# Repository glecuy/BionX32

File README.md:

# BionX32  stm32 controller for BionX ebike motor

The BionX motor has originally a built-in controller. This project aims to replace embedde electronics by an external controller.
Regular 24V controller with square waves doesn't provide good enough results, this is a new attempt with a FOC implementation.

## Project Content

3 phases output,

3 hall sensors input,

One Shunt current measurement,

Interface for S866 Display.

PAS input,

Brake input

Core code is generated thanks to ST micro graphical tools. (X-CUBE-MCSDK)
then adapted to STM32F103C8Tx

## Hardware description

STM32 module
MOSFET module
Main pcb
S866 display

## Credits  & Resources
STM32CubeIDE

STM32 MC SDK (motor control software development kit) : Gived up (Did not work for me)

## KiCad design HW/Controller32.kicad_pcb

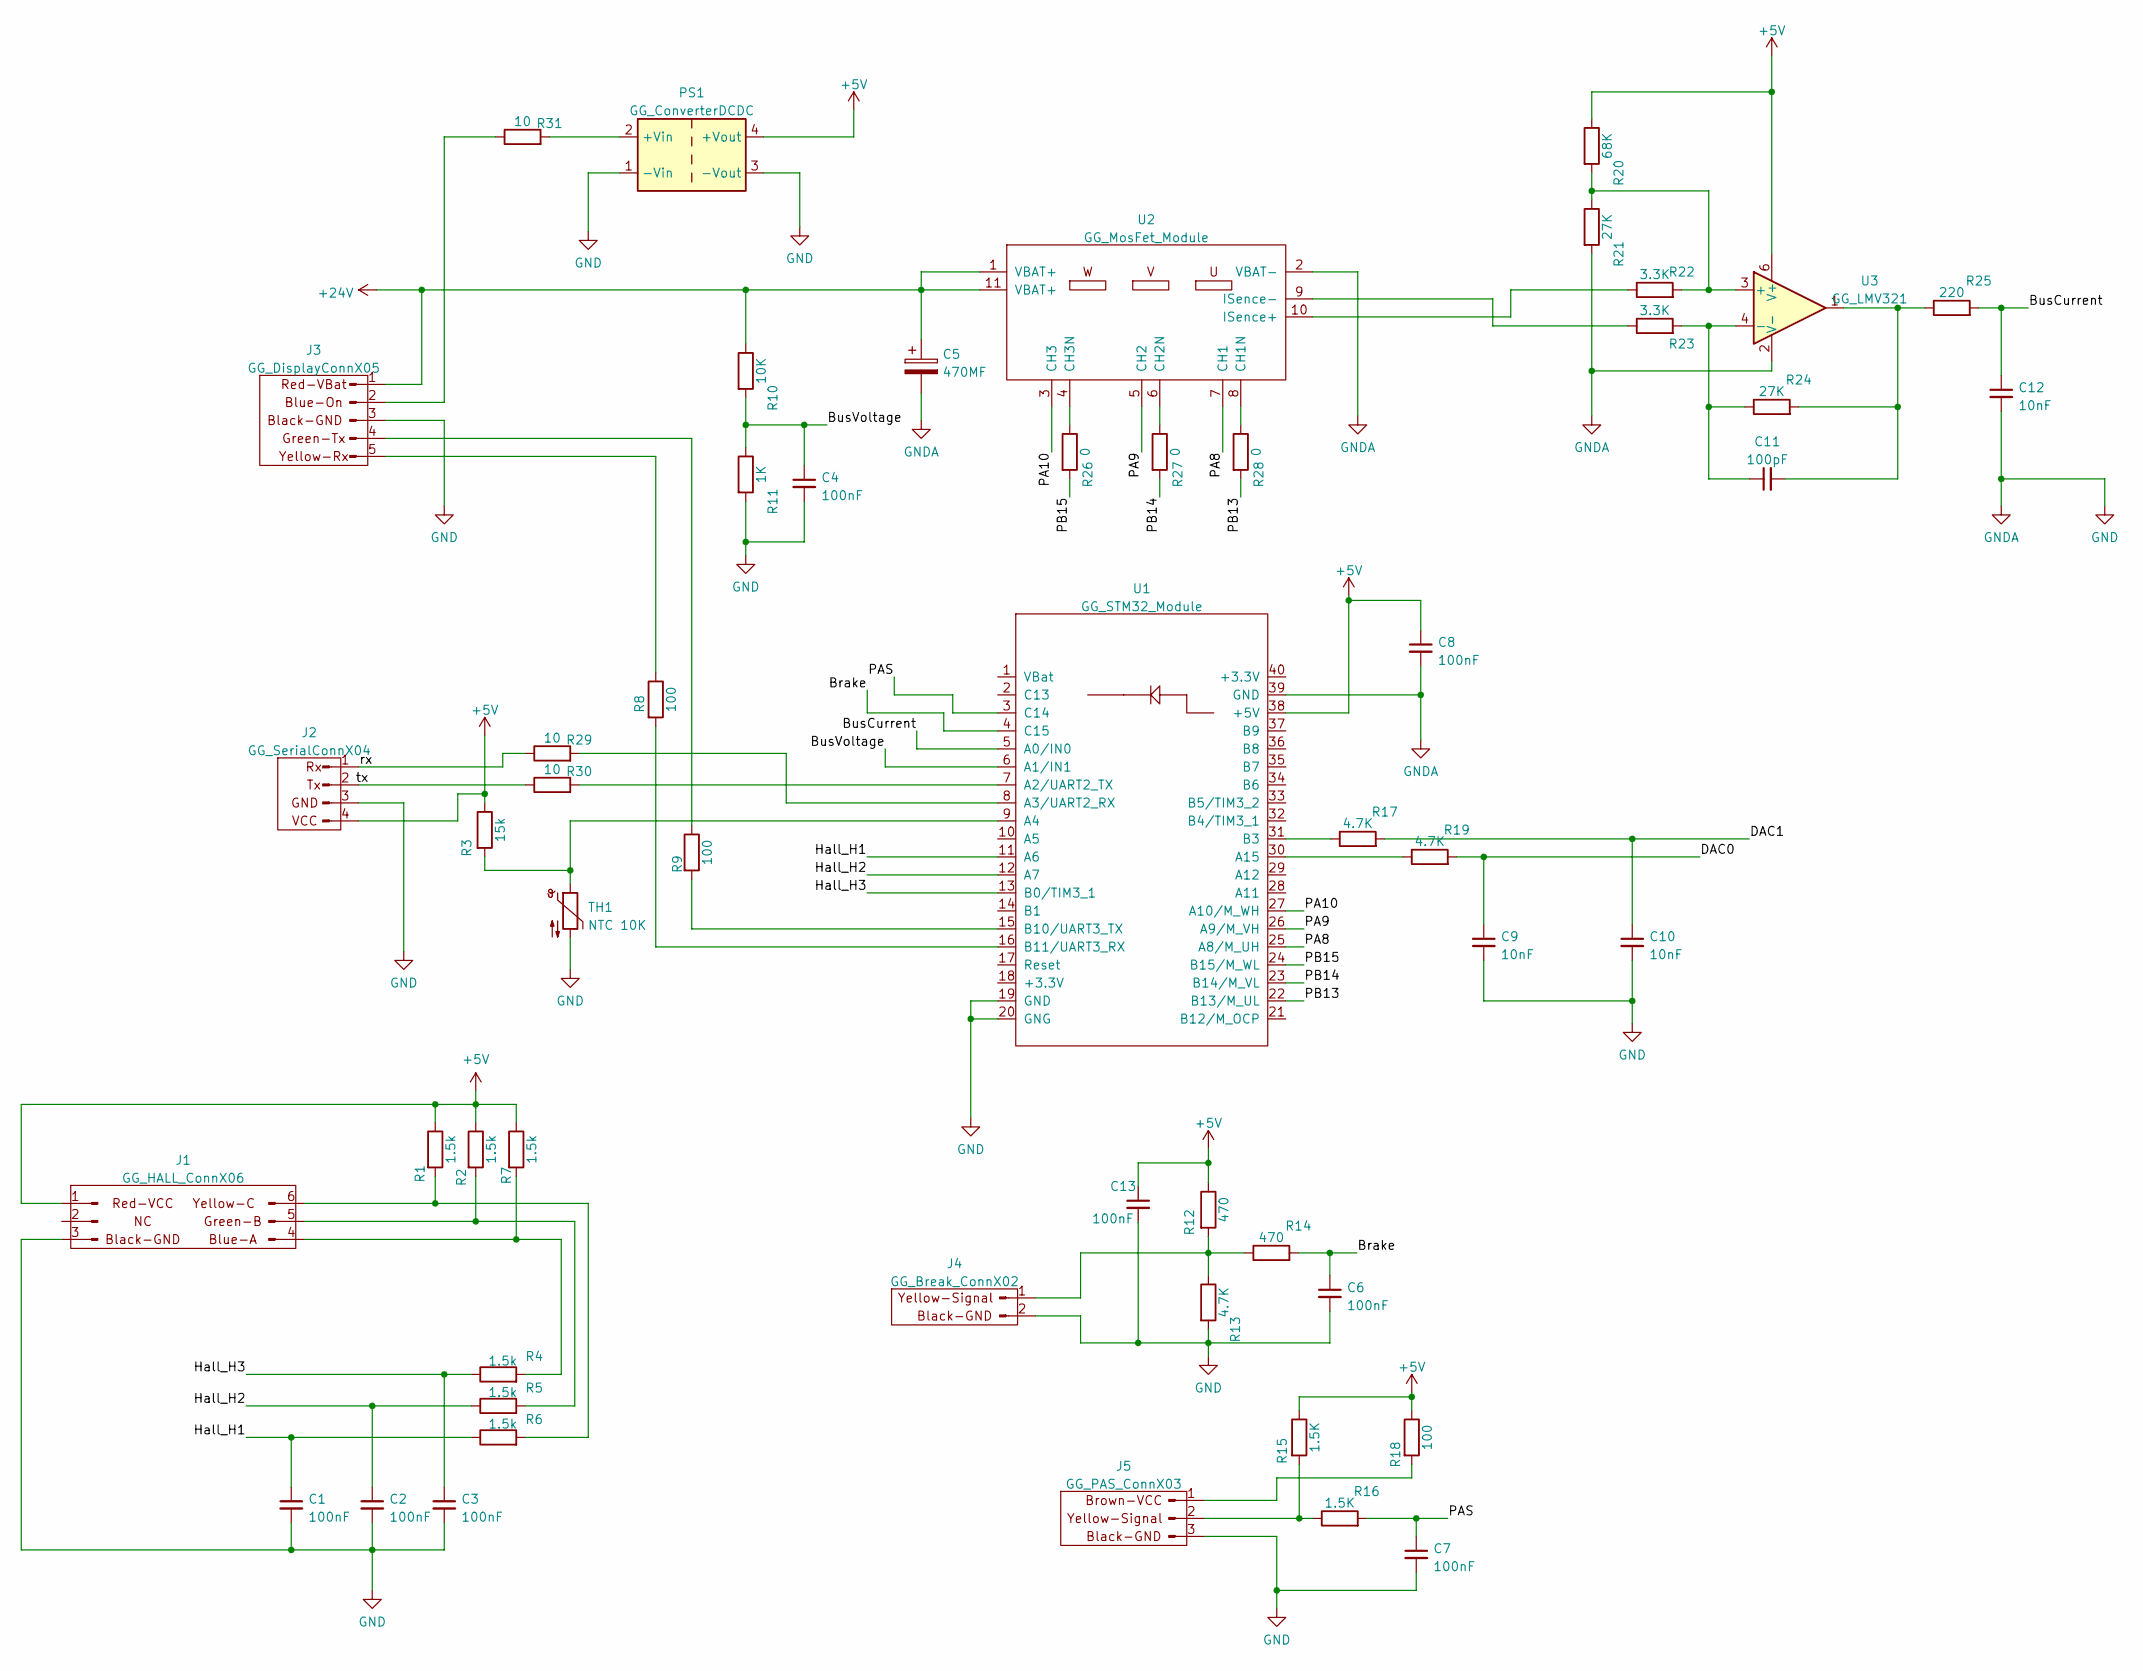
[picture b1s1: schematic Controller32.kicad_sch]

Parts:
C1, C2, C3, C4, C6, C7, C8, C13: 100nF; GG_C_0805
C5: 470MF; GG_CP_L30.0mm_D15.0mm_Horizontal
C9, C10, C12: 10nF; GG_C_0805
C11: 100pF; GG_C_0805
J1: GG_HALL_ConnX06; GG_6Wires_P2.54mm
J2: GG_SerialConnX04; GG_Serial04_P2.54mm
J3: GG_DisplayConnX05; GG_5Wires_P2.54mm
J4: GG_Break_ConnX02; GG_2Wires_P2.54mm
J5: GG_PAS_ConnX03; GG_3Wires_P2.54mm
PS1: GG_ConverterDCDC; GG_X0018_DCDC
R1, R2, R4, R5, R6, R7: 1.5k; GG_R_1206
R3: 15k; GG_R_1206
R8, R9, R18: 100; GG_R_1206
R10: 10K; GG_R_1206
R11: 1K; GG_R_1206
R12, R14: 470; GG_R_1206
R13, R17, R19: 4.7K; GG_R_1206
R15, R16: 1.5K; GG_R_1206
R20: 68K; GG_R_1206
R21, R24: 27K; GG_R_1206
R22, R23: 3.3K; GG_R_1206
R25: 220; GG_R_1206
R26, R27, R28: 0; GG_R_1206
R29, R30, R31: 10; GG_R_1206
TH1: NTC 10K; GG_2Wires_P2.54mm
U1: GG_STM32_Module; GG_STM32_DIP-40
U2: GG_MosFet_Module; GG_MOSFET_Moule
U3: GG_LMV321; SOT-23-6_Handsoldering

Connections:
+5V: C8.1, C13.1, J1.1, J2.4, PS1.4 (+Vout), R1.1, R2.1, R3.1, R7.1, R12.1, R15.1, R18.1, R20.1, U1.38 (+5V), U3.6 (V+)
+24V: C5.1, J3.1, R10.1, U2.1 (VBAT+), U2.11 (VBAT+)
/Brake: C6.1, R14.2, U1.4 (C15)
/BusCurrent: C12.1, R25.2, U1.5 (A0/IN0)
/BusVoltage: C4.1, R10.2, R11.1, U1.6 (A1/IN1)
/DAC0: C9.1, R19.2
/DAC1: C10.1, R17.2
/Hall_H1: C1.1, R6.1, U1.11 (A6)
/Hall_H2: C2.1, R5.1, U1.12 (A7)
/Hall_H3: C3.1, R4.1, U1.13 (B0/TIM3_1)
/PA8: U1.25 (A8/M_UH), U2.7 (CH1)
/PA9: U1.26 (A9/M_VH), U2.5 (CH2)
/PA10: U1.27 (A10/M_WH), U2.3 (CH3)
/PAS: C7.1, R16.2, U1.3 (C14)
/PB13: R28.2, U1.22 (B13/M_UL)
/PB14: R27.2, U1.23 (B14/M_VL)
/PB15: R26.2, U1.24 (B15/M_WL)
/rx: J2.1, R29.1
GND: C1.2, C2.2, C3.2, C4.2, C5.2, C6.2, C7.2, C8.2, C9.2, C10.2, C12.2, C13.2, J1.3, J2.3, J3.3, J4.2, J5.3, PS1.1 (-Vin), PS1.3 (-Vout), R11.2, R13.2, R21.2, TH1.2, U1.19 (GND), U1.20 (GNG), U1.39 (GND), U2.2 (VBAT-), U3.2 (V-)
unnamed: C11.1, R23.2, R24.1, U3.4 (-)
unnamed: C11.2, R24.2, R25.1, U3.1
unnamed: J1.4, R4.2, R7.2
unnamed: J1.5, R2.2, R5.2
unnamed: J1.6, R1.2, R6.2
unnamed: J2.2, R30.1
unnamed: J3.2, R31.1
unnamed: J3.4, R9.1
unnamed: J3.5, R8.1
unnamed: J4.1, R12.2, R13.1, R14.1
unnamed: J5.1, R18.2
unnamed: J5.2, R15.2, R16.1
unnamed: PS1.2 (+Vin), R31.2
unnamed: R3.2, TH1.1, U1.9 (A4)
unnamed: R8.2, U1.16 (B11/UART3_RX)
unnamed: R9.2, U1.15 (B10/UART3_TX)
unnamed: R17.1, U1.31 (B3)
unnamed: R19.1, U1.30 (A15)
unnamed: R20.2, R21.1, R22.2, U3.3 (+)
unnamed: R22.1, U2.10 (ISence+)
unnamed: R23.1, U2.9 (ISence-)
unnamed: R26.1, U2.4 (CH3N)
unnamed: R27.1, U2.6 (CH2N)
unnamed: R28.1, U2.8 (CH1N)
unnamed: R29.2, U1.8 (A3/UART2_RX)
unnamed: R30.2, U1.7 (A2/UART2_TX)

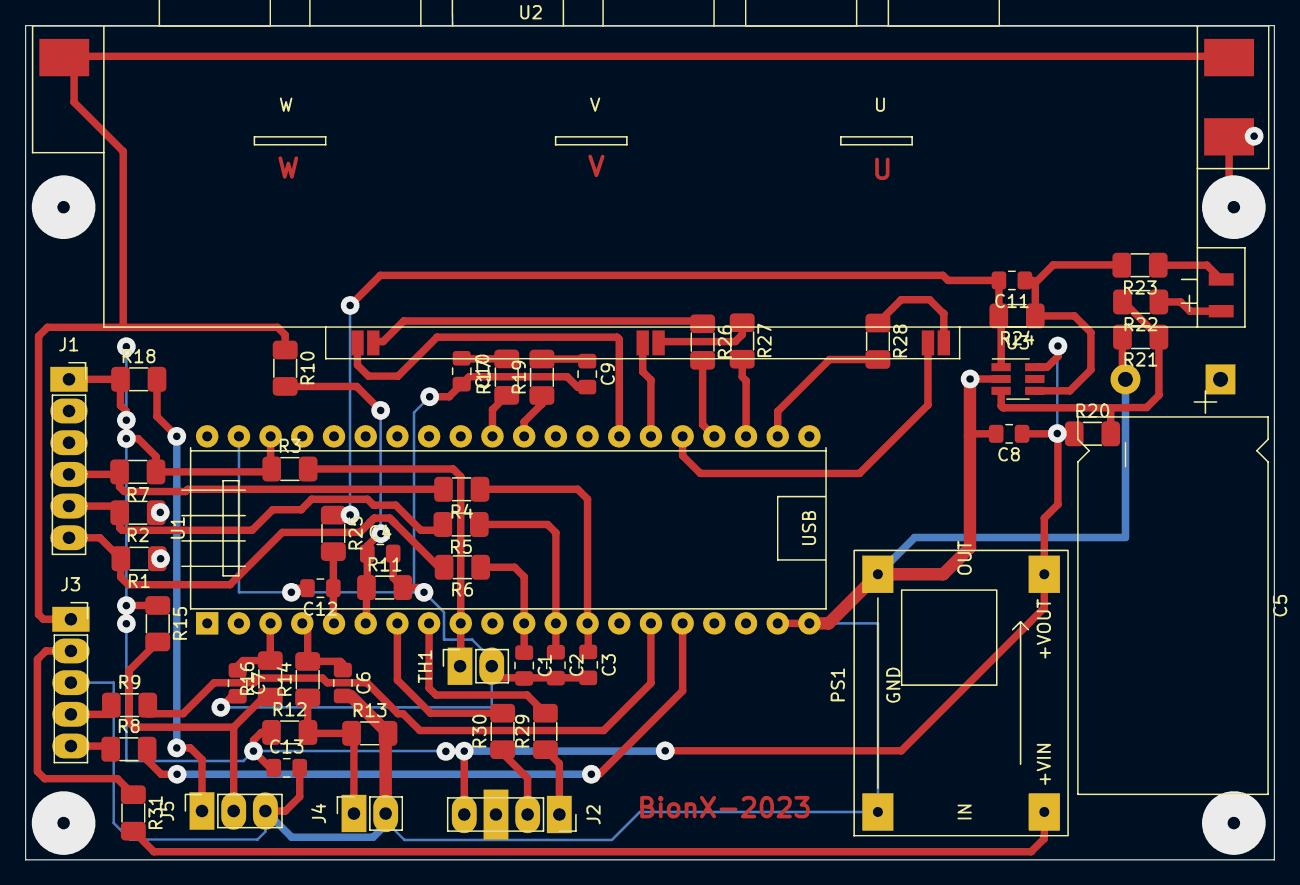
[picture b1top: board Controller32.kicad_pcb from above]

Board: 2 copper layers, 100.1 x 66.9 mm, 54 parts (0 on the bottom side), 45 nets.

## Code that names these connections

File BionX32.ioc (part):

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Mcu.Name=STM32F103C(8-B)Tx
Mcu.Package=LQFP48
Mcu.UserName=STM32F103C8Tx
PA0-WKUP.Signal=ADCx_IN0
PA1.Signal=ADCx_IN1
PA10.Signal=S_TIM1_CH3
PA11.Signal=S_TIM1_CH4
PA13.Mode=Serial_Wire
PA13.Signal=SYS_JTMS-SWDIO
PA14.Mode=Serial_Wire
PA14.Signal=SYS_JTCK-SWCLK
PA15.Signal=S_TIM2_CH1_ETR
PA2.Mode=Asynchronous
PA2.Signal=USART2_TX
PA3.Mode=Asynchronous
PA3.Signal=USART2_RX
PA4.Signal=ADCx_IN4
PA5.GPIOParameters=GPIO_Label
PA5.GPIO_Label=Probe01
PA5.Signal=GPIO_Output
PA6.GPIOParameters=GPIO_Label
PA6.GPIO_Label=Hall_H1
PA6.Signal=S_TIM3_CH1
PA7.GPIOParameters=GPIO_Label
PA7.GPIO_Label=Hall_H2
PA7.Signal=S_TIM3_CH2
PA8.Signal=S_TIM1_CH1
PA9.Signal=S_TIM1_CH2
PB0.GPIOParameters=GPIO_Label
PB0.GPIO_Label=Hall_H3
PB0.Signal=S_TIM3_CH3
PB10.Mode=Asynchronous
PB10.Signal=USART3_TX
PB11.Mode=Asynchronous
PB11.Signal=USART3_RX
PB13.Mode=PWM Generation1 CH1 CH1N
PB13.Signal=TIM1_CH1N
PB14.Mode=PWM Generation2 CH2 CH2N
PB14.Signal=TIM1_CH2N
PB15.Mode=PWM Generation3 CH3 CH3N
PB15.Signal=TIM1_CH3N
PB3.Signal=S_TIM2_CH2
PC13-TAMPER-RTC.GPIOParameters=GPIO_Label
PC13-TAMPER-RTC.GPIO_Label=BlueLED
PC13-TAMPER-RTC.Signal=GPIO_Output
PD0-OSC_IN.Mode=HSE-External-Oscillator
PD0-OSC_IN.Signal=RCC_OSC_IN
PD1-OSC_OUT.Mode=HSE-External-Oscillator
PD1-OSC_OUT.Signal=RCC_OSC_OUT
RCC.SYSCLKFreq_VALUE=72000000
RCC.SYSCLKSource=RCC_SYSCLKSOURCE_PLLCLK
board=custom

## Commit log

2022-09-11 Initial code, UART_Printf, s866 com OK
2022-09-11 Update README.md
    Fix and cleanup README.
2022-09-14 New generated code for motor control
2022-09-17 revert communication with display (NOT FIXED)
2022-09-23 Fix Display communication
2022-09-25 Fix and tune display Rx Tx, start MC interface
2022-10-01 Add ADC voltage and temperature
2022-10-02 Convert all files with dos2unix
2023-02-12 Update from MotorSDK, implement PAS input
2025-11-02 Restart project without ST motor SDK - Back to a simpler 6 steps driving mode
2025-11-02 Implement assist level control from Display
2025-11-04 Display and controller work together. (speed and assist level)
2025-11-11 experimental code around svpwm
2025-11-11 Back to main branch
